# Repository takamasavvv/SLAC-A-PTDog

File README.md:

# SLAC-A-PTDog
Power management, Telemetry and Watch dog

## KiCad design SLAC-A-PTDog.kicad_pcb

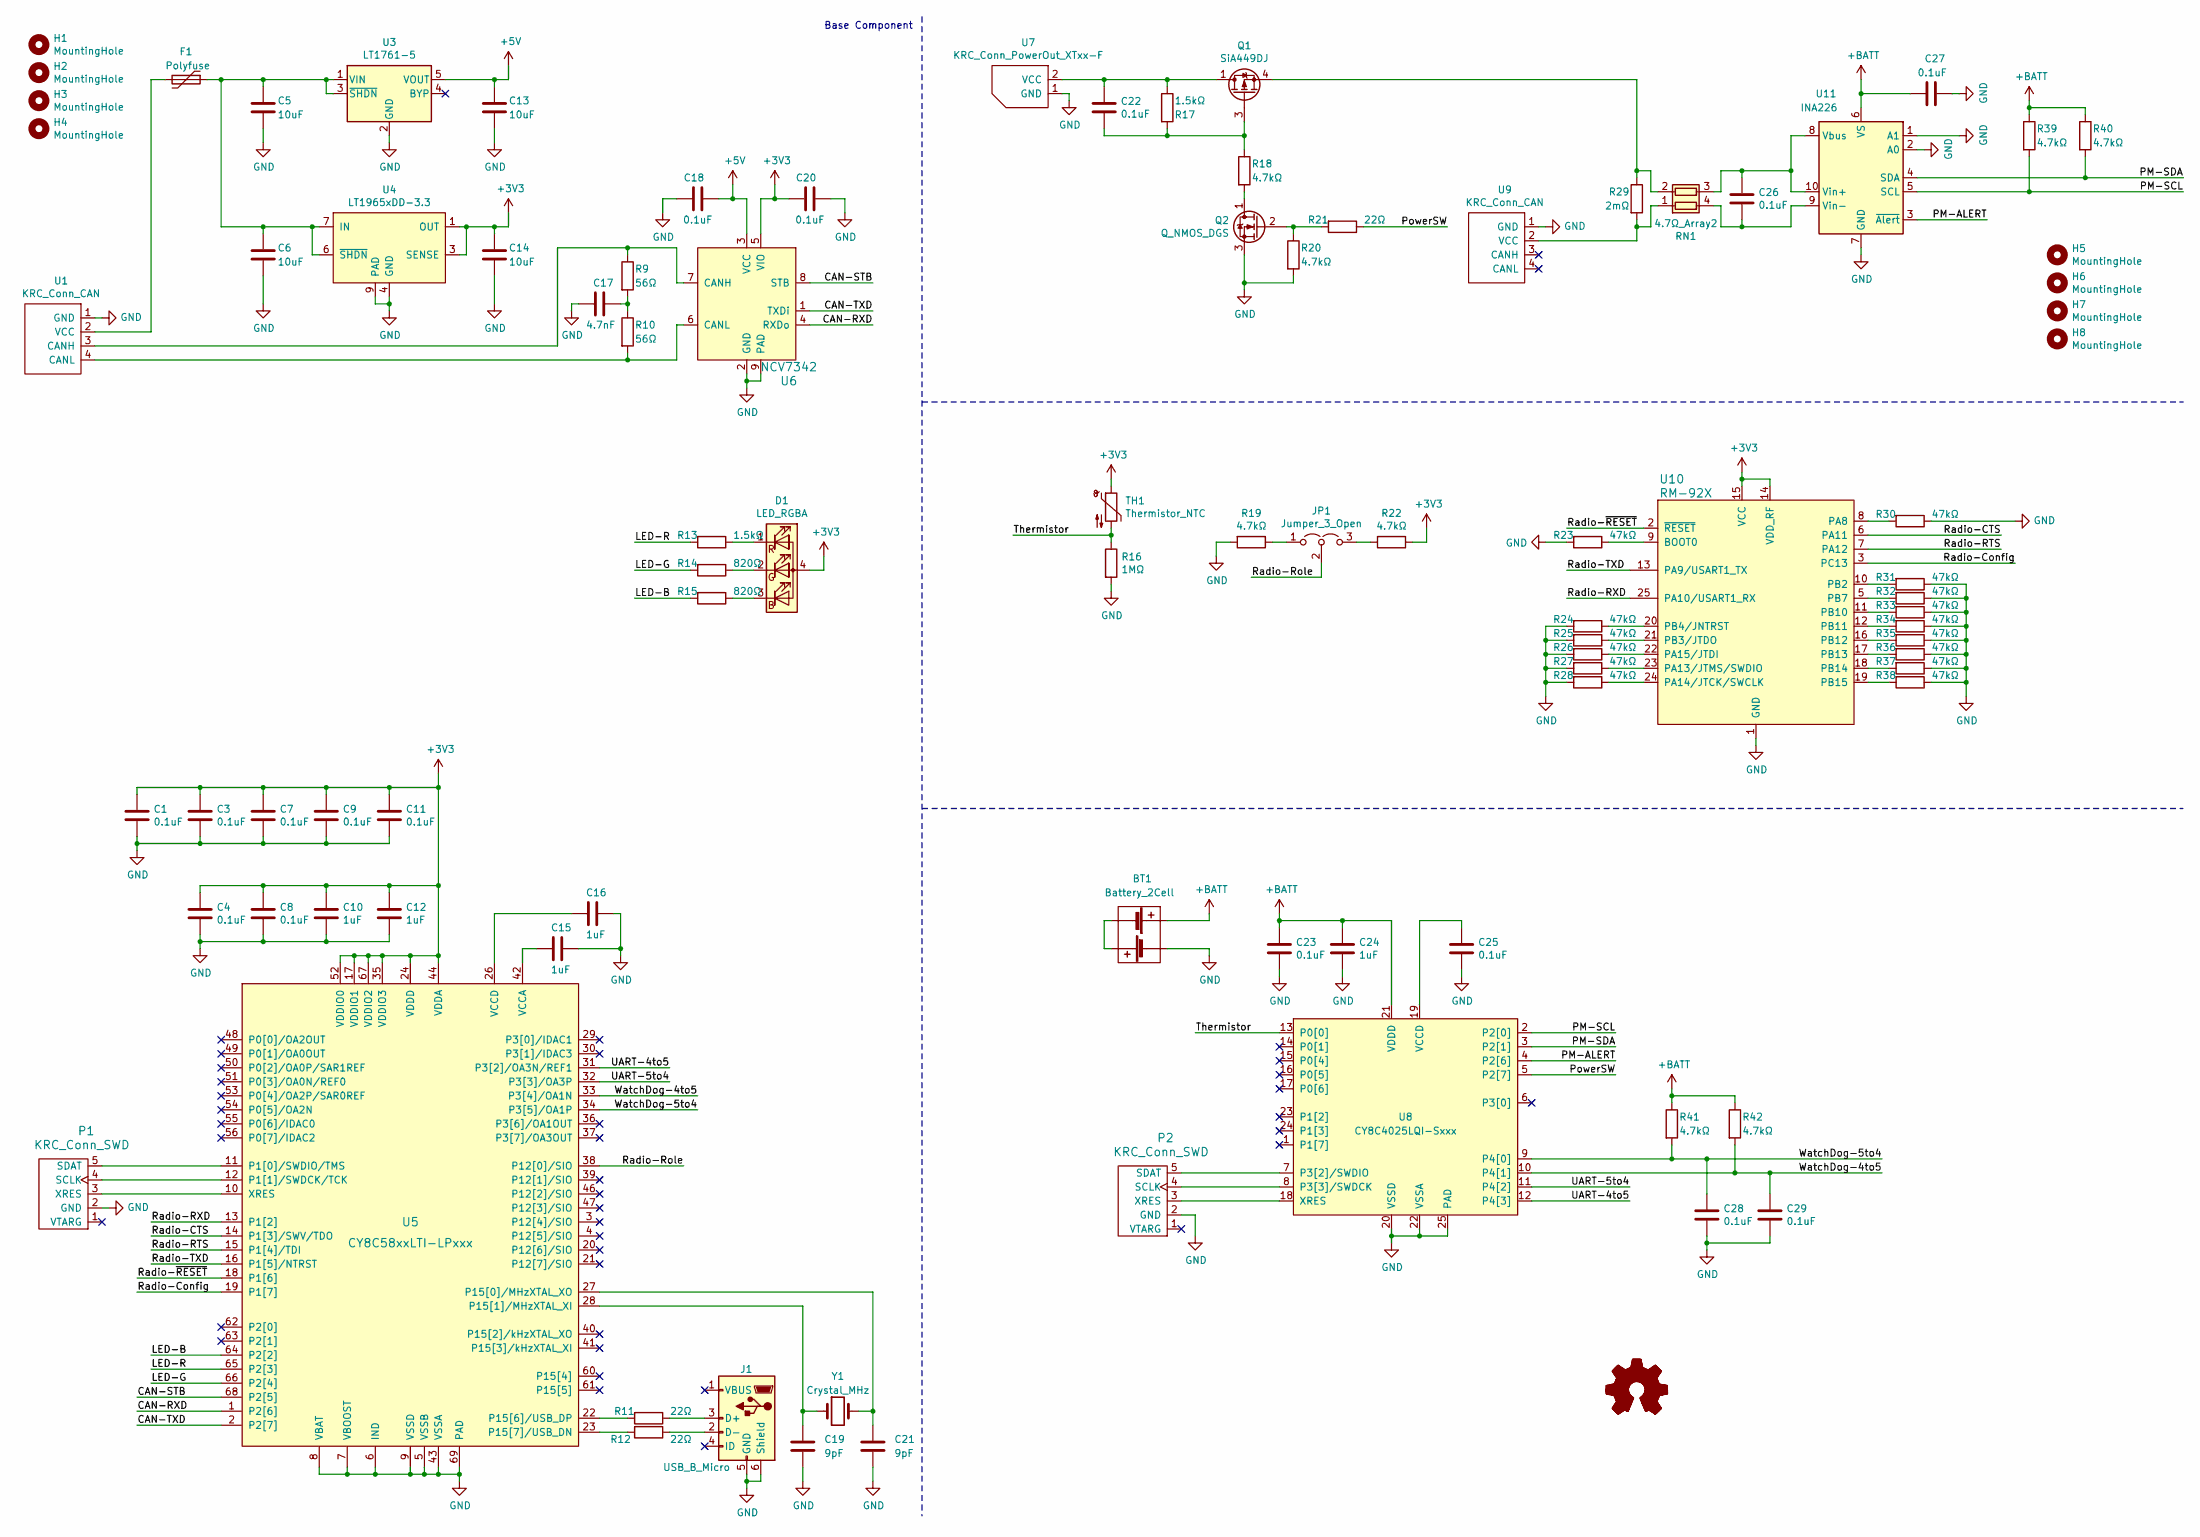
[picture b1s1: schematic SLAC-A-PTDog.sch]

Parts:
BT1: Battery_2Cell; BatteryHolder_Keystone_1022_2xAA; MPN 1022
C1, C3, C4, C7, C8, C9, C11, C18, C20, C22, C23, C25, C26, C27, C28, C29: 0.1uF; C_0402_1005Metric; MPN GRM155R71H104KE14J
C5, C6, C13, C14: 10uF; C_0603_1608Metric; MPN GRM188R61E106MA73D
C10, C12, C15, C16, C24: 1uF; C_0402_1005Metric; MPN GRM155R61E105KA12D
C17: 4.7nF; C_0402_1005Metric; MPN GRM155R71H472KA01D
C19, C21: 9pF; C_0201_0603Metric; MPN GRM0335C1E9R0CA01D
D1: LED_RGBA; LED_LiteOn_LTST-C19HE1WT; MPN LTST-C19HE1WT
F1: Polyfuse; Fuse_0805_2012Metric; MPN MF-FSMF035X-2
H1, H2, H3, H4, H5, H6, H7, H8: MountingHole; MountingHole_3.2mm_M3
J1: USB_B_Micro; Hirose_ZX_ZX62D-B-5P8; MPN ZX62D-B-5P8(30)
JP1: Jumper_3_Open; SolderJumper-3_P1.3mm_Open_Pad1.0x1.5mm
P1, P2: KRC_Conn_SWD; JST_JQ_05JQ-BT_1x05_P2.5mm_Vertical; MPN 05JQ-BT
Q1: SiA449DJ; Vishay_PowerPAK_SC70-6L_Single; MPN SiA449DJ
Q2: Q_NMOS_DGS; SOT-23; MPN 2N7002K
R9, R10: 56Ω; R_0402_1005Metric; MPN ERJ-2GEJ560X
R11, R12, R21: 22Ω; R_0402_1005Metric; MPN ERJ-2GEJ220X
R13, R17: 1.5kΩ; R_0402_1005Metric; MPN ERJ-2GEJ152X
R14, R15: 820Ω; R_0402_1005Metric; MPN ERJ-2GEJ821X
R16: 1MΩ; R_0402_1005Metric; MPN ERJ-2GEJ105X
R18, R20, R39, R40, R41, R42: 4.7kΩ; R_0402_1005Metric; MPN ERJ-2GEJ472X
R19, R22: 4.7kΩ; R_0402_1005Metric
R23, R24, R25, R26, R27, R28, R30, R31, R32, R33, R34, R35, R36, R37, R38: 47kΩ; R_0402_1005Metric; MPN ERJ-2GEJ473X
R29: 2mΩ; R_0805_2012Metric; MPN PMR10EZPFV2L00
RN1: 4.7Ω_Array2; R_Array_EXB14V; MPN EXB-24V4R7JX
TH1: Thermistor_NTC; R_0603_1608Metric; MPN B57330V2103J260
U1, U9: KRC_Conn_CAN; JST_XH_S4B-XH-A_1x04_P2.50mm_Horizontal; MPN S4B-XH-A
U3: LT1761-5; TSOT-23-5; MPN LT1761MPS5-5#TRMPBF
U4: LT1965xDD-3.3; DFN-8-1EP_3x3mm_P0.5mm_EP1.66x2.38mm; MPN LT1965EDD-3.3#PBF
U5: CY8C58xxLTI-LPxxx; Cypress_QFN-68_EP_8x8_Pitch0.4mm; MPN CY8C5868LTI-LP039
U6: NCV7342; DFN-8-1EP_3x3mm_P0.65mm_EP1.55x2.4mm; MPN NCV7342MW3R2G
U7: KRC_Conn_PowerOut_XTxx-F; AMASS_XT30U-M_1x02_P5.0mm_Vertical
U8: CY8C4025LQI-Sxxx; QFN-24-1EP_4x4mm_P0.5mm_EP2.6x2.6mm; MPN CY8C4025LQI-S401
U10: RM-92X; RFLink_Module_RM-92A; MPN RM-92A
U11: INA226; VSSOP-10_3x3mm_P0.5mm
Y1: Crystal_MHz; Crystal_Murata_XRCHA; MPN XRCHA24M000F0A01R0

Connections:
+3V3: C1.1, C3.1, C4.1, C7.1, C8.1, C9.1, C10.1, C11.1, C12.1, C14.1, C20.1, D1.4 (A), R22.1, TH1.1, U4.1 (OUT), U4.2 (OUT), U4.3 (SENSE), U5.17 (VDDIO1), U5.24 (VDDD), U5.35 (VDDIO3), U5.44 (VDDA), U5.52 (VDDIO0), U5.59 (VDDD), U5.67 (VDDIO2), U6.5 (VIO), U10.14 (VDD_RF), U10.15 (VCC)
+5V: C13.1, C18.2, U3.5 (VOUT), U6.3 (VCC)
+BATT: BT1.1 (+), C23.1, C24.1, C27.2, R39.1, R40.1, R41.1, R42.1, U8.21 (VDDD), U11.6 (VS)
/CAN-RXD: U5.1 (P2[6]), U6.4 (RXDo)
/CAN-STB: U5.68 (P2[5]), U6.8 (STB)
/CAN-TXD: U5.2 (P2[7]), U6.1 (TXDi)
/LED-B: R15.2, U5.64 (P2[2])
/LED-G: R14.2, U5.66 (P2[4])
/LED-R: R13.2, U5.65 (P2[3])
/PM-ALERT: U8.4 (P2[6]), U11.3 (~Alert~)
/PM-SCL: R39.2, U8.2 (P2[0]), U11.5 (SCL)
/PM-SDA: R40.2, U8.3 (P2[1]), U11.4 (SDA)
/PowerSW: R21.1, U8.5 (P2[7])
/Radio-CTS: U5.14 (P1[3]/SWV/TDO), U10.6 (PA11)
/Radio-Config: U5.19 (P1[7]), U10.3 (PC13)
/Radio-RTS: U5.15 (P1[4]/TDI), U10.7 (PA12)
/Radio-RXD: U5.13 (P1[2]), U10.25 (PA10/USART1_RX)
/Radio-Role: JP1.2 (C), U5.38 (P12[0]/SIO)
/Radio-TXD: U5.16 (P1[5]/NTRST), U10.13 (PA9/USART1_TX)
/Radio-~RESET: U5.18 (P1[6]), U10.2 (~RESET)
/Thermistor: R16.1, TH1.2, U8.13 (P0[0])
/UART-4to5: U5.31 (P3[2]/OA3N/REF1), U8.12 (P4[3])
/UART-5to4: U5.32 (P3[3]/OA3P), U8.11 (P4[2])
/WatchDog-4to5: C29.1, R42.2, U5.33 (P3[4]/OA1N), U8.10 (P4[1])
/WatchDog-5to4: C28.1, R41.2, U5.34 (P3[5]/OA1P), U8.9 (P4[0])
GND: BT1.4 (-), C1.2, C3.2, C4.2, C5.2, C6.2, C7.2, C8.2, C9.2, C10.2, C11.2, C12.2, C13.2, C14.2, C15.1, C16.1, C17.2, C18.1, C19.2, C20.2, C21.2, C23.2, C24.2, C25.2, C27.1, C28.2, C29.2, J1.5 (GND), J1.6 (Shield), P1.2 (GND), P2.2 (GND), Q2.3 (S), R16.2, R19.2, R20.2, R23.2, R24.2, R25.2, R26.2, R27.2, R28.2, R30.1, R31.1, R32.1, R33.1, R34.1, R35.1, R36.1, R37.1, R38.1, U1.1 (GND), U3.2 (GND), U4.4 (GND), U4.5 (GND), U4.9 (PAD), U5.5 (VSSB), U5.6 (IND), U5.7 (VBOOST), U5.8 (VBAT), U5.9 (VSSD), U5.25 (VSSD), U5.43 (VSSA), U5.45 (VSSD), U5.58 (VSSD), U5.69 (PAD), U6.2 (GND), U6.9 (PAD), U7.1 (GND), U8.20 (VSSD), U8.22 (VSSA), U8.25 (PAD), U9.1 (GND), U10.1 (GND), U10.26 (GND), U11.1 (A1), U11.2 (A0), U11.7 (GND)
unnamed: BT1.2 (-), BT1.3 (+)
unnamed: C5.1, C6.1, F1.1, U3.1 (VIN), U3.3 (~SHDN), U4.6 (~SHDN), U4.7 (IN), U4.8 (IN)
unnamed: C15.2, U5.42 (VCCA)
unnamed: C16.2, U5.26 (VCCD), U5.57 (VCCD)
unnamed: C17.1, R9.2, R10.1
unnamed: C19.1, U5.28 (P15[1]/MHzXTAL_XI), Y1.1
unnamed: C21.1, U5.27 (P15[0]/MHzXTAL_XO), Y1.2
unnamed: C22.1, Q1.1 (D), R17.1, U7.2 (VCC)
unnamed: C22.2, Q1.3 (G), R17.2, R18.1
unnamed: C25.1, U8.19 (VCCD)
unnamed: C26.1, RN1.3 (R2.2), U11.8 (Vbus), U11.10 (Vin+)
unnamed: C26.2, RN1.4 (R1.2), U11.9 (Vin-)
unnamed: D1.1 (RK), R13.1
unnamed: D1.2 (GK), R14.1
unnamed: D1.3 (BK), R15.1
unnamed: F1.2, U1.2 (VCC)
unnamed: J1.2 (D-), R12.1
unnamed: J1.3 (D+), R11.1
unnamed: JP1.1 (A), R19.1
unnamed: JP1.3 (B), R22.2
unnamed: P1.3 (XRES), U5.10 (XRES)
unnamed: P1.4 (SCLK), U5.12 (P1[1]/SWDCK/TCK)
unnamed: P1.5 (SDAT), U5.11 (P1[0]/SWDIO/TMS)
unnamed: P2.3 (XRES), U8.18 (XRES)
unnamed: P2.4 (SCLK), U8.8 (P3[3]/SWDCK)
unnamed: P2.5 (SDAT), U8.7 (P3[2]/SWDIO)
unnamed: Q1.4 (S), R29.1, RN1.2 (R2.1)
unnamed: Q2.1 (D), R18.2
unnamed: Q2.2 (G), R20.1, R21.2
unnamed: R9.1, U1.3 (CANH), U6.7 (CANH)
unnamed: R10.2, U1.4 (CANL), U6.6 (CANL)
unnamed: R11.2, U5.22 (P15[6]/USB_DP)
unnamed: R12.2, U5.23 (P15[7]/USB_DN)
unnamed: R23.1, U10.9 (BOOT0)
unnamed: R24.1, U10.20 (PB4/JNTRST)
unnamed: R25.1, U10.21 (PB3/JTDO)
unnamed: R26.1, U10.22 (PA15/JTDI)
unnamed: R27.1, U10.23 (PA13/JTMS/SWDIO)
unnamed: R28.1, U10.24 (PA14/JTCK/SWCLK)
unnamed: R29.2, RN1.1 (R1.1), U9.2 (VCC)
unnamed: R30.2, U10.8 (PA8)
unnamed: R31.2, U10.10 (PB2)
unnamed: R32.2, U10.5 (PB7)
unnamed: R33.2, U10.11 (PB10)
unnamed: R34.2, U10.12 (PB11)
unnamed: R35.2, U10.16 (PB12)
unnamed: R36.2, U10.17 (PB13)
unnamed: R37.2, U10.18 (PB14)
unnamed: R38.2, U10.19 (PB15)

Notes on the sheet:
Base Component

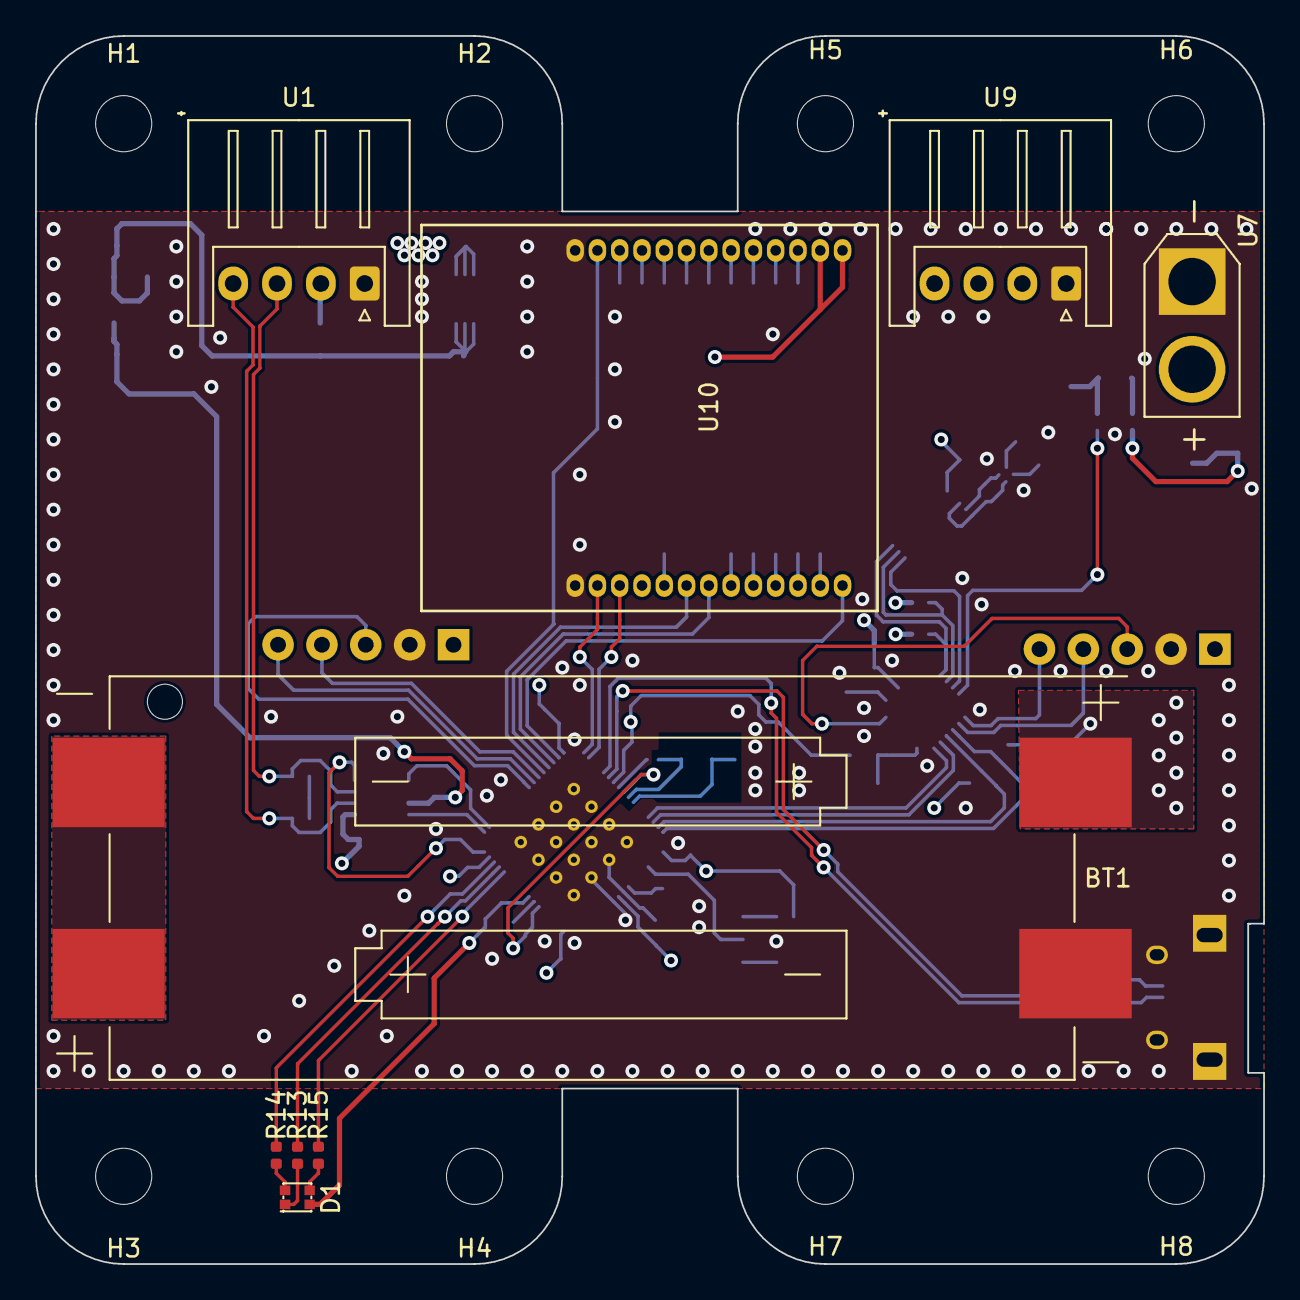
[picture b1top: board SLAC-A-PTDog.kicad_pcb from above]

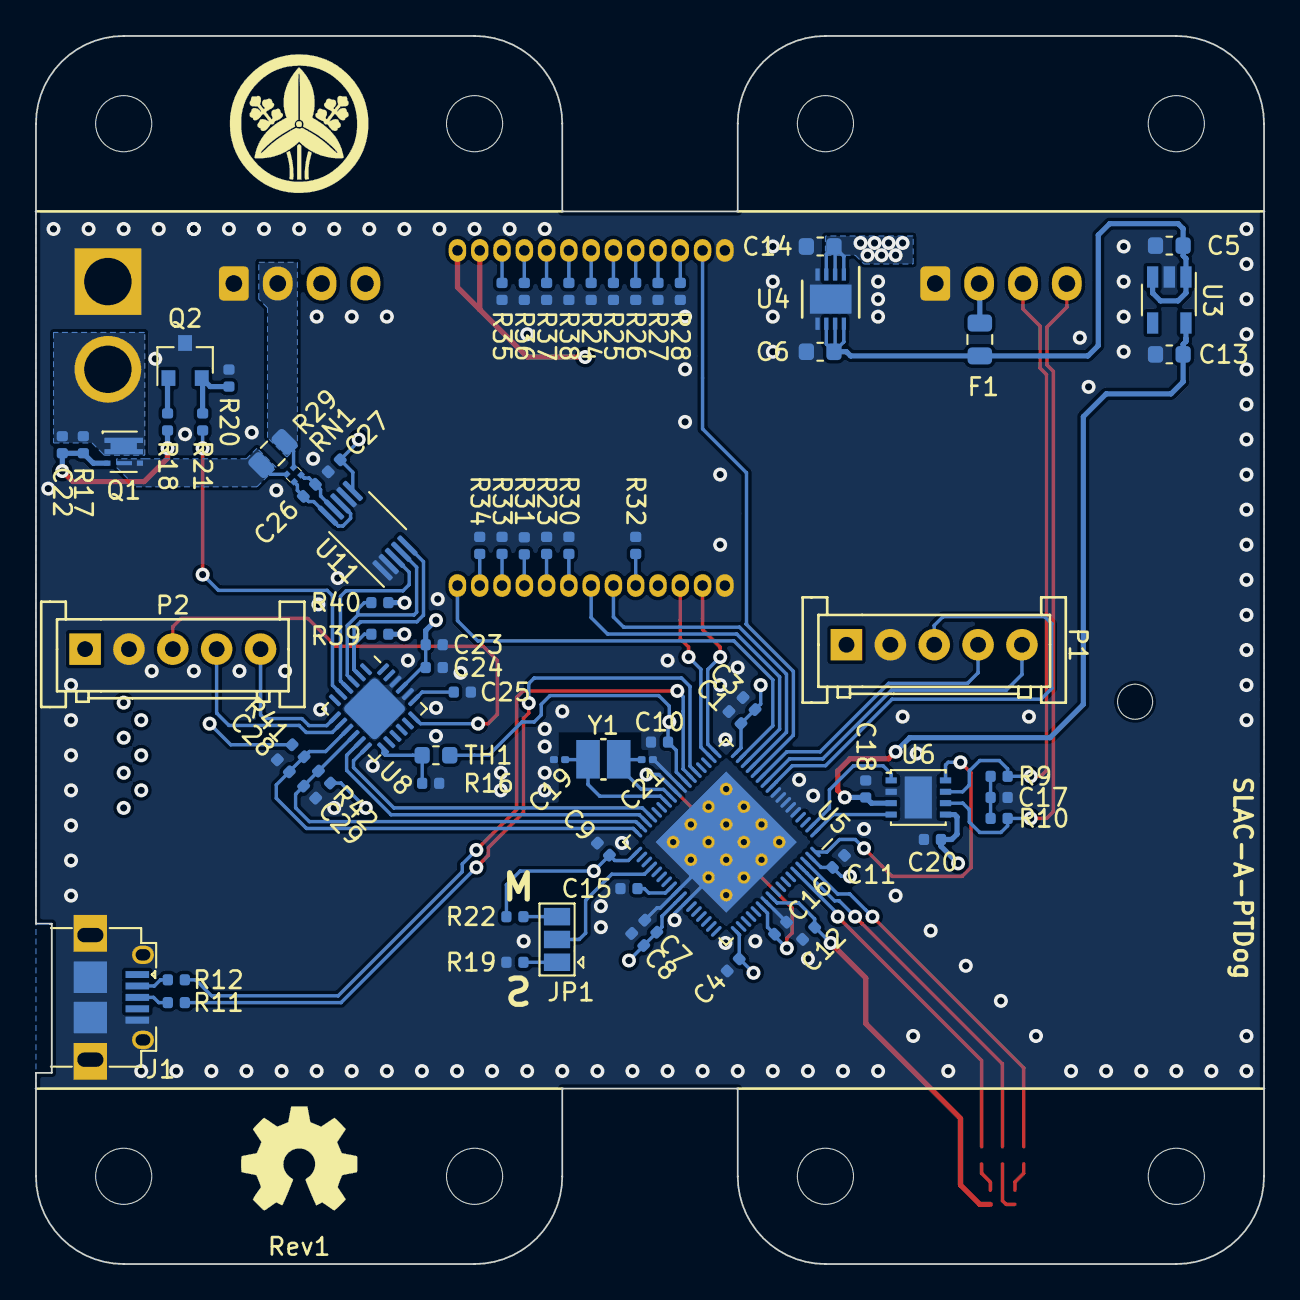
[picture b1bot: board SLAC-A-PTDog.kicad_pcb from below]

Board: 4 copper layers, 70.0 x 70.0 mm, 92 parts (75 on the bottom side), 75 nets.

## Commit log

2020-02-02 complete rev 1
